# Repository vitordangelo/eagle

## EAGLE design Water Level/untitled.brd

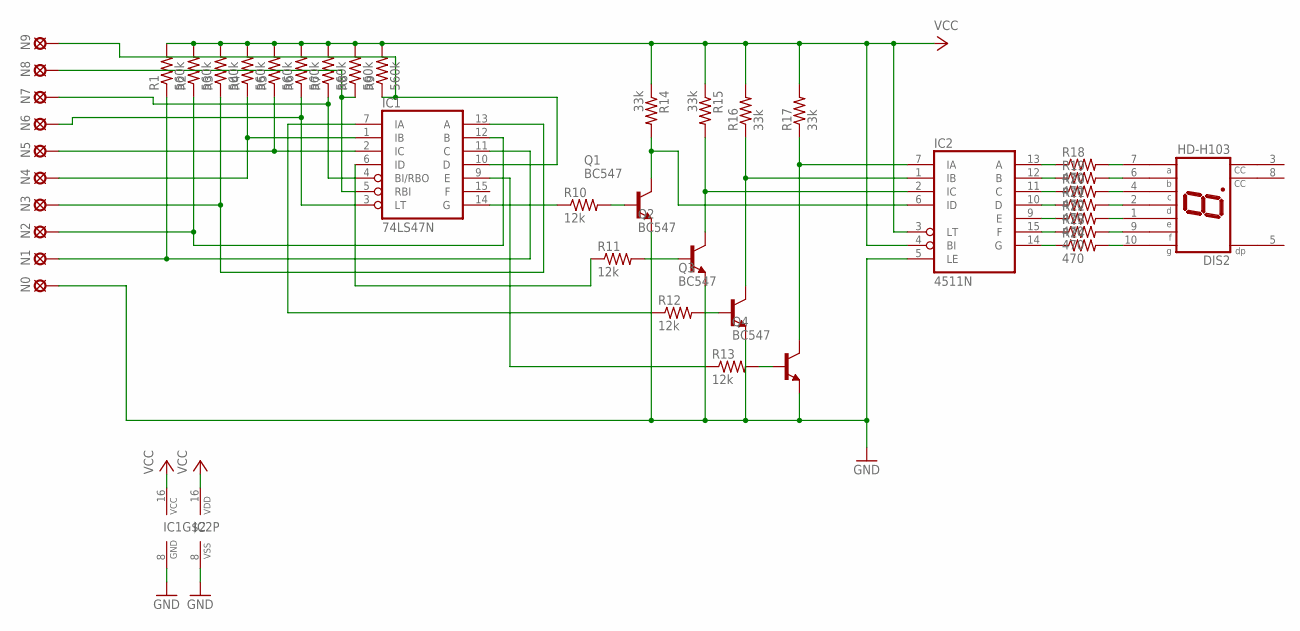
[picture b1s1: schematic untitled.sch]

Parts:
DIS2: HD-H103; HDSP-M
IC1: 74LS47N; DIL16
IC2: 4511N; DIL16
N0, N1, N2, N3, N4, N5, N6, N7, N8, N9: LSP10
Q1, Q2, Q3, Q4: BC547; TO92
R1, R2, R3, R4, R5, R6, R7, R8, R9: 560k; 0204/7
R10, R11, R12, R13: 12k; 0204/7
R14, R15, R16, R17: 33k; 0204/7
R18, R19, R20, R21, R22, R23, R24: 470; 0204/7

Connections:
GND: IC1.8 (GND), IC2.5 (LE), IC2.8 (VSS), N0.MP, Q1.1 (E), Q2.1 (E), Q3.1 (E), Q4.1 (E)
unnamed: IC1.11 (C), N1.MP, R1.1
unnamed: IC1.12 (B), N2.MP, R2.1
unnamed: Q1.2 (B), R10.2
unnamed: IC1.13 (A), N3.MP, R3.1
unnamed: IC1.1 (IB), N4.MP, R4.1
unnamed: IC1.2 (IC), N5.MP, R5.1
unnamed: IC1.4 (BI/RBO), N7.MP, R7.1
unnamed: IC1.5 (RBI), N8.MP, R8.1
unnamed: IC1.10 (D), N9.MP, R9.1
unnamed: IC1.14 (G), R10.1
unnamed: IC1.3 (LT), N6.MP, R6.1
unnamed: DIS2.10 (G), R24.2
unnamed: Q2.2 (B), R11.2
unnamed: IC1.6 (ID), R11.1
unnamed: IC2.6 (ID), Q1.3 (C), R14.2
unnamed: Q3.2 (B), R12.2
unnamed: IC1.7 (IA), R12.1
unnamed: IC2.2 (IC), Q2.3 (C), R15.2
unnamed: Q4.2 (B), R13.2
unnamed: IC1.9 (E), R13.1
unnamed: IC2.1 (IB), Q3.3 (C), R16.1
unnamed: IC2.13 (A), R18.1
unnamed: IC2.12 (B), R19.1
unnamed: IC2.11 (C), R20.1
unnamed: IC2.10 (D), R21.1
unnamed: IC2.9 (E), R22.1
unnamed: IC2.15 (F), R23.1
unnamed: IC2.14 (G), R24.1
unnamed: DIS2.7 (A), R18.2
unnamed: DIS2.6 (B), R19.2
unnamed: DIS2.4 (C), R20.2
unnamed: DIS2.2 (D), R21.2
unnamed: DIS2.1 (E), R22.2
unnamed: DIS2.9 (F), R23.2
unnamed: IC2.7 (IA), Q4.3 (C), R17.1
VCC: IC1.16 (VCC), IC2.3 (LT), IC2.4 (BI), IC2.16 (VDD), R1.2, R2.2, R3.2, R4.2, R5.2, R6.2, R7.2, R8.2, R9.2, R14.1, R15.1, R16.2, R17.2

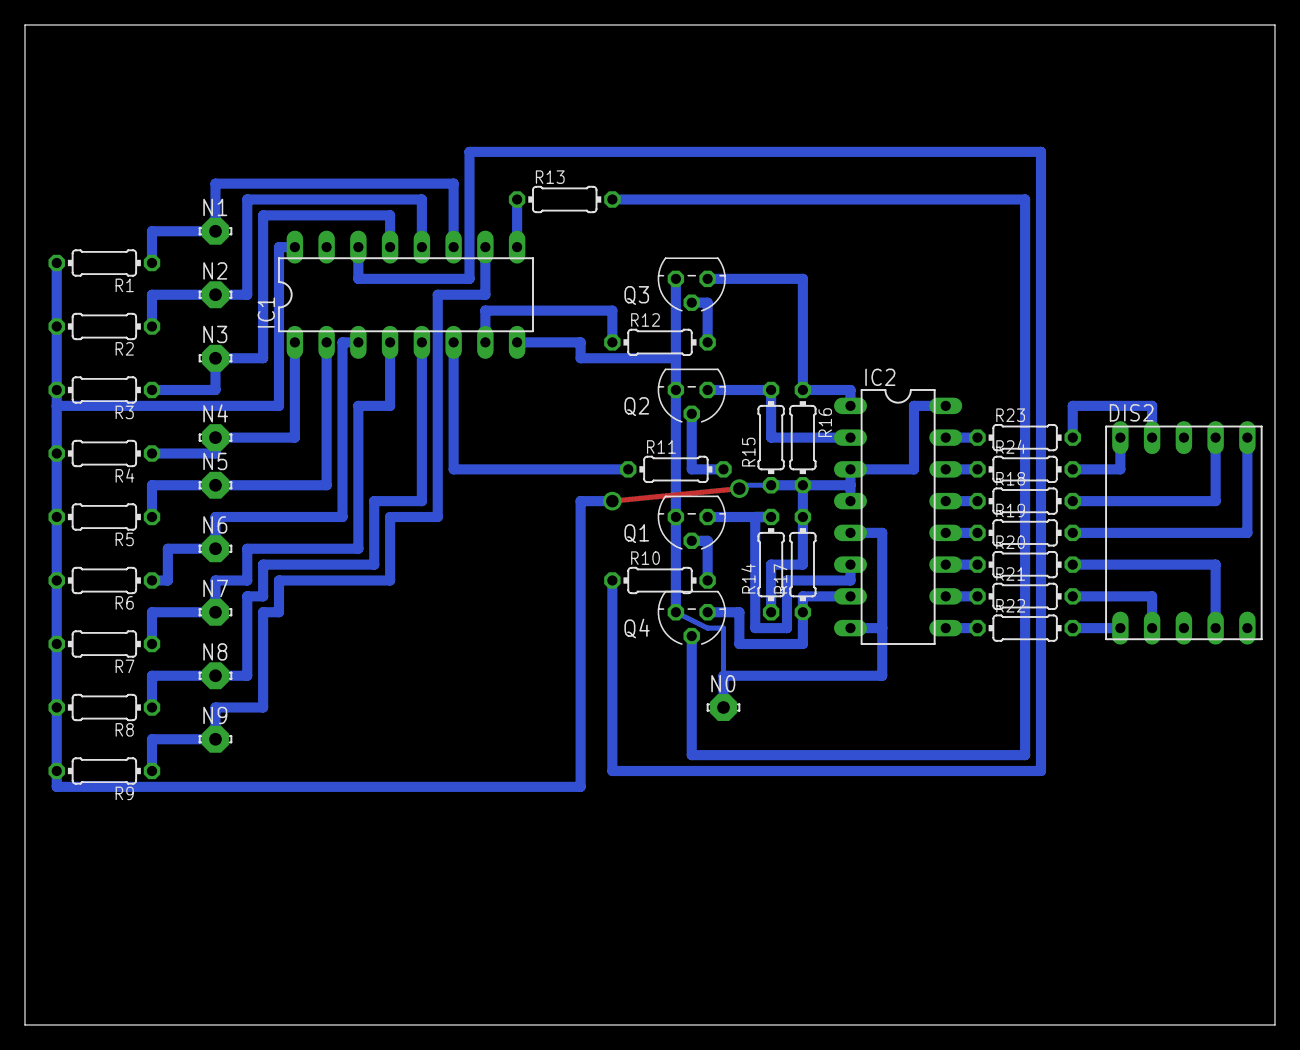
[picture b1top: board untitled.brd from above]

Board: 2 copper layers, 100.0 x 80.0 mm, 41 parts (0 on the bottom side), 37 nets.
